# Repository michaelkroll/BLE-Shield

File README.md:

## BLE-Shield

The MIT License (MIT)
Copyright (c) 2012-2015 Dr. Michael Kroll
 
Permission is hereby granted, free of charge, to any person obtaining a copy of this software and associated 
documentation files (the "Software"), to deal in the Software without restriction, including without limitation 
the rights to use, copy, modify, merge, publish, distribute, sublicense, and/or sell copies of the Software, 
and to permit persons to whom the Software is furnished to do so, subject to the following conditions:
 
The above copyright notice and this permission notice shall be included in all copies or substantial portions of the Software.
 
THE SOFTWARE IS PROVIDED "AS IS", WITHOUT WARRANTY OF ANY KIND, EXPRESS OR IMPLIED, INCLUDING BUT NOT 
LIMITED TO THE WARRANTIES OF MERCHANTABILITY, FITNESS FOR A PARTICULAR PURPOSE AND NONINFRINGEMENT. IN 
NO EVENT SHALL THE AUTHORS OR COPYRIGHT HOLDERS BE LIABLE FOR ANY CLAIM, DAMAGES OR OTHER LIABILITY, 
WHETHER IN AN ACTION OF CONTRACT, TORT OR OTHERWISE, ARISING FROM, OUT OF OR IN CONNECTION WITH THE 
SOFTWARE OR THE USE OR OTHER DEALINGS IN THE SOFTWARE.

### Content

This repository contains the eagle design files as well as the firmware source code and precompiled hex files.
Moreover I added the Arduino Sketches from my blog to this repository.

### Latest Version

The Latest version of the BLE-Shield is v3.0.0 as illustrated in the image below.

#### Services and Characteristics of the BLE-Shield v3.0.0

The new BLE-Shield supports some new services and haracteristics. The RX and TX characteristics are not combined into one indicating Data characteristic
Moreover the Bluegiga OTA Service is supported enabling you to update the BLE-Shield over the air using e.g. the iOS App BLExplr.

##### BLE-Shield Service v3.0.0 (B4BDB998-8F4A-45F6-A407-6B48D79CFC2F)

###### Bluetooth Device Address Characteristic (B4BDB998-8F4B-45F6-A407-6B48D79CFC2F)

This characteristic is read only and used to retrieve the Bluetooth Device Address of the BLE113-M256k module.

###### Baudrate Characteristic (B4BDB998-8F4C-45F6-A407-6B48D79CFC2F)

This characteristic is read and write and used to set the BLE-Shields baudrate. The default baudrate is 9600 baud
It is a one byte characteristic. The following baudrates are suported and can be set using the following byte set to the
characteristic:

Baudrate  | Configuration Byte
--------- | ------------------
9600      | 0x00
14400     | 0x01
19200     | 0x02
28800     | 0x03
38400     | 0x04
57600     | 0x05
115200    | 0x06

###### Enable Connect LED characteristic (B4BDB998-8F4D-45F6-A407-6B48D79CFC2F)

This characteristic is used to control the connection LED on the BLE-Shield. The LED is per default off.
In order to change it's behavior write e.g. 0xff the the characteristic to make it lit on the next connection.

LED State | Configuration Byte
--------- | ------------------
OFF       | 0x00
ON        | 0xff

###### Data characteristic (B4BDB998-8F4E-45F6-A407-6B48D79CFC2F)

The new BLE-Shield v3.0.0 uses a Data characteristic to send and receive data. In order to support this
the characteristic is a write and indicate characteristic. On BLExplr it is no longer necessary to switch between
RX and TX characteristics. You can stay on the same screen to see data which is recevied while you are transmitting data.

##### Bluegiga OTA Service (1d14d6ee-fd63-4fa1-bfa4-8f47b42119f0)

This is the implementation of Bluegiga's OTA Service to update the firmware over the air.

###### Data characteristic (f7bf3564-fb6d-4e53-88a4-5e37e0326063)

Bluegiga OTA Control Characteristic

###### Data characteristic (984227f3-34fc-4045-a5d0-2c581f81a153)

Bluegiga OTA Data Characteristic

### Links
* http://www.mkroll.mobi
* http://forum.mkroll.mobi

### Notes:
* The Eagle design files are created using Eagle v5.11.0 - v7.1 depending on the version of the BLE-Shield. BLE-Shield v3.0.0 was designed with Eagle v7.1.0
* The Firmware v1.0.0 and v1.0.1 for the BLE112 module on the BLE-Shield was created and compiled for the Bluegiga BLE112 SDK v1.0.3 Build 43
* The Firmware v3.0.0 was developed using Bluegiga's BLE SDK v1.3.2 Build 122.
* The Arduino Sketches have been tested with Arduino 1.0.1
* the Arduino Sketched vor BLE-Shield v3.0.0 has been tested with Arduino v1.0.6 on OSX
* The .NETMF Sample has been tested with Microsoft Visual C# Express 2010, .NET Micro Framework SDK v4.2 and the Netduino SDK v4.2.2.0 (32-bit) running on a NetDuino2

## .NETMF support 
The latest addition to this repository is .NETMF support. With a little help of Thomas Amberg @tamberg I added a sample project for 
the NetDuino2 board available at http://www.netduino.com which shows how use the BLE-Shield with this platform.  

## BLE-Shield iPhone App for the BLE-Shield v1.0.0

The iPhone App was part of the BLE-Shield Kickstarter campaign https://www.kickstarter.com/projects/rowdyrobot/arduino-ble-shield-connecting-the-ios-and-the-ardu and only
supports the BLE-Shield v1.0.0 The BLE-Shield app provides access to the BLE-Shield Service and their characteristics. It's user interface is implemented like 
a chat application. The chart partners are the BLE-Shield and the iPhone, illustrated by small icons.

Once the BLE-Shield is connected, the application will automatically enable notifications on the RX characteristic. So whenever 
the BLE-Shield's 16 byte buffer is filled completely, the buffer will be notified to the iPhone. 

The app was developed using Xcode 4.5.2, iOS6 SDK and tested on an iPhone4S and iPhone5 running iOS6.0.1

*Screenshots*

. 
. 
. 
. 
. 
. 

### Used third party components

* BLEUtils taken from the TI SensorTag App, created by Ole Andreas Torvmark 
* MBProgressHUD created by Matej Bukovinski https://github.com/matej/MBProgressHUD
* PTSMessagingCell created by Ralph Grasser https://github.com/ppanopticon/PTSMessagingCell/

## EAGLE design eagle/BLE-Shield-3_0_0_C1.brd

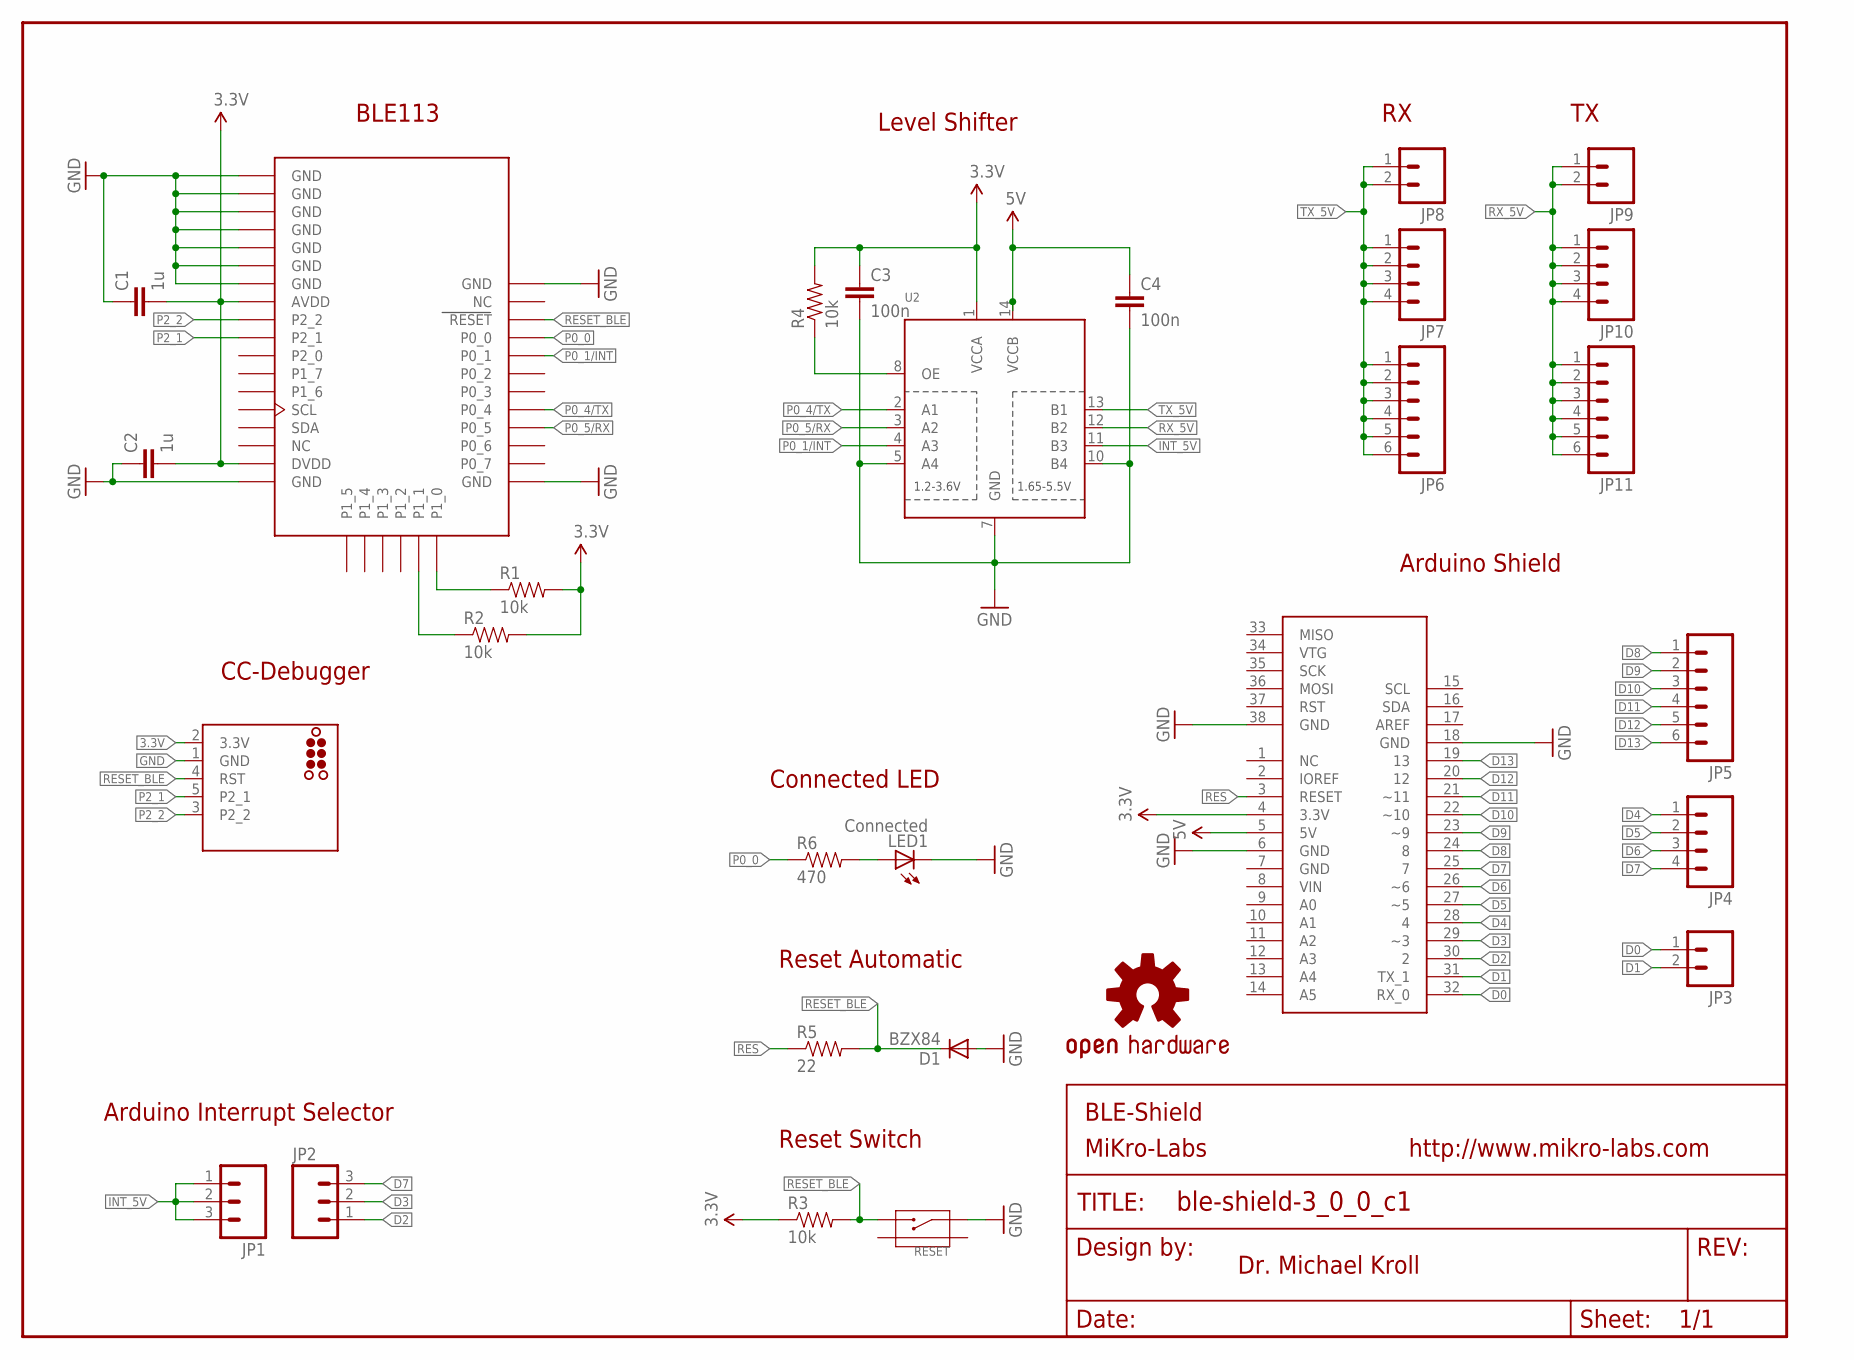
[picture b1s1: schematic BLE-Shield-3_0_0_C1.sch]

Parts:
C1, C2: 1u; 0603-CAP
C3, C4: 100n; 0603-CAP
CC-DEBUGGER: TC2030-CC-DEBUGGER; TC2030-MCP-NL
D1: BZX84; SOT23-3
FRAME1: FRAME-LETTER; CREATIVE_COMMONS
JP1, JP2: M03PTH; 1X03
JP3, JP8, JP9: M02PTH; 1X02
JP4, JP7, JP10: M04PTH; 1X04
JP5, JP6, JP11: M06SIP; 1X06
LED1: Connected; LED-0603
LOGO1: OSHW-LOGOS; OSHW-LOGO-S
R1, R2, R3, R4: 10k; 0603-RES
R5: 22; 0603-RES
R6: 470; 0603-RES
RESET: BUTTON-2P-REINFORCE-3100060P1; 4P-SMD-7.0X3.5X3.5H-90D
U1: BLE113-A-VISUAL; BLE113-A
U2: TXB0104PWR; TSSOP14
U$1: ARDUINO_UNO_SHIELD_ICSP_PADS_ONLY; ICSP_PADS_ONLY

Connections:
3.3V: C1.2, C2.2, C3.1, CC-DEBUGGER.2 (3.3V), R1.2, R2.2, R3.1, R4.2, U1.AVDD, U1.DVDD, U2.1 (VCCA), U$1.4 (3.3V)
5V: C4.1, U2.14 (VCCB), U$1.5 (5V)
D0: JP3.1, U$1.32 (RX_0)
D1: JP3.2, U$1.31 (TX_1)
D2: JP2.1, U$1.30 (2)
D3: JP2.2, U$1.29 (~3)
D4: JP4.1, U$1.28 (4)
D5: JP4.2, U$1.27 (~5)
D6: JP4.3, U$1.26 (~6)
D7: JP2.3, JP4.4, U$1.25 (7)
D8: JP5.1, U$1.24 (8)
D9: JP5.2, U$1.23 (~9)
D10: JP5.3, U$1.22 (~10)
D11: JP5.4, U$1.21 (~11)
D12: JP5.5, U$1.20 (12)
D13: JP5.6, U$1.19 (13)
GND: C1.1, C2.1, C3.2, C4.2, CC-DEBUGGER.1 (GND), D1.1 (A), LED1.C, RESET.1, U1.GND, U1.GND@2 (GND), U1.GND@3 (GND), U1.GND@4 (GND), U1.GND@5 (GND), U1.GND@6 (GND), U1.GND@7 (GND), U1.GND@8 (GND), U1.GND@9 (GND), U1.GND@10 (GND), U2.5 (A4), U2.7 (GND), U2.10 (B4), U$1.6 (GND), U$1.18 (GND), U$1.38 (GND)
INT_5V: JP1.1, JP1.2, JP1.3, U2.11 (B3)
unnamed: LED1.A, R6.2
unnamed: R4.1, U2.8 (OE)
unnamed: R1.1, U1.P1_0
unnamed: R2.1, U1.P1_1
P0_0: R6.1, U1.P0_0
P0_1/INT: U1.P0_1, U2.4 (A3)
P0_4/TX: U1.P0_4, U2.2 (A1)
P0_5/RX: U1.P0_5, U2.3 (A2)
P2_1: CC-DEBUGGER.5 (P2_1), U1.P2_1
P2_2: CC-DEBUGGER.3 (P2_2), U1.P2_2
RES: R5.1, U$1.3 (RESET)
RESET_BLE: CC-DEBUGGER.4 (RST), D1.3 (C), R3.2, R5.2, RESET.2, U1.RESET
RX_5V: JP9.1, JP9.2, JP10.1, JP10.2, JP10.3, JP10.4, JP11.1, JP11.2, JP11.3, JP11.4, JP11.5, JP11.6, U2.12 (B2)
TX_5V: JP6.1, JP6.2, JP6.3, JP6.4, JP6.5, JP6.6, JP7.1, JP7.2, JP7.3, JP7.4, JP8.1, JP8.2, U2.13 (B1)

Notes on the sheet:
BLE113
CC-Debugger
Arduino Shield
Level Shifter
Reset Switch
Reset Automatic
Connected LED
Arduino Interrupt Selector
BLE-Shield
MiKro-Labs
http://www.mikro-labs.com
Dr. Michael Kroll

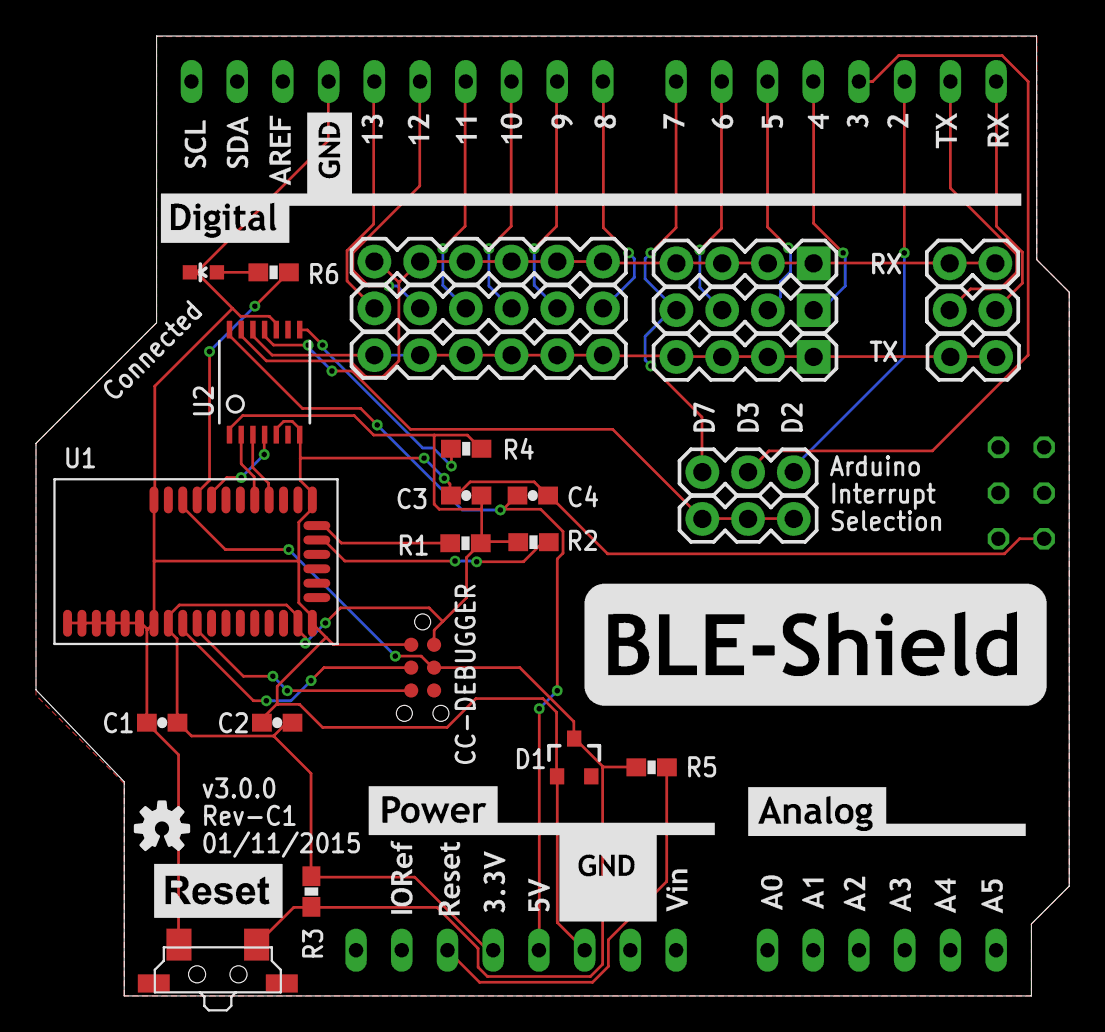
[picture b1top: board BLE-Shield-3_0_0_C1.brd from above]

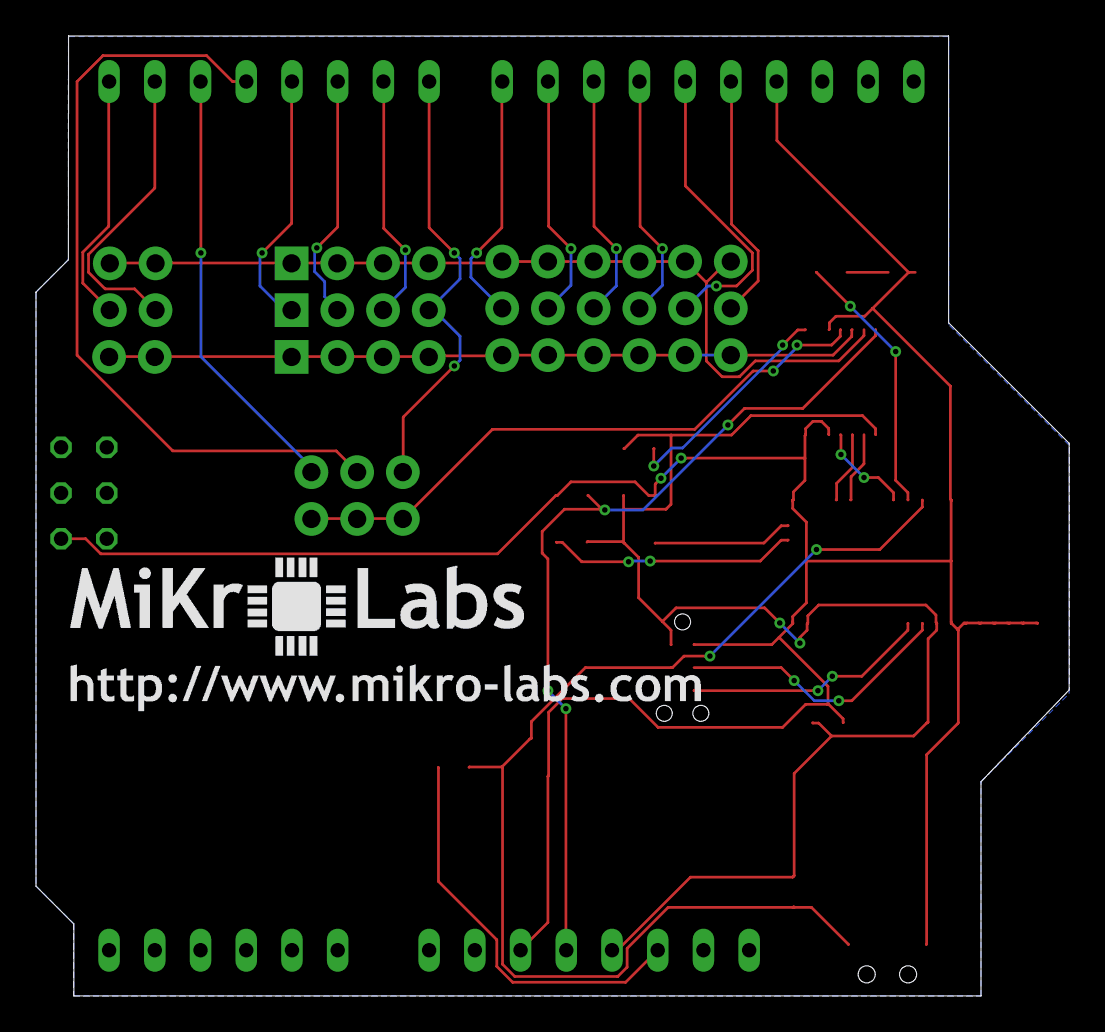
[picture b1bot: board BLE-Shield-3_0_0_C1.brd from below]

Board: 4 copper layers, 57.4 x 53.3 mm, 36 parts (2 on the bottom side), 32 nets.

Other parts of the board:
U$2: DIGITAL
U$3: POWER-ANALOG
U$4: MIKROLABS-URL
U$5: MIKROLABS-LOGO
U$6: BLE-SHIELD
U$7: RESET

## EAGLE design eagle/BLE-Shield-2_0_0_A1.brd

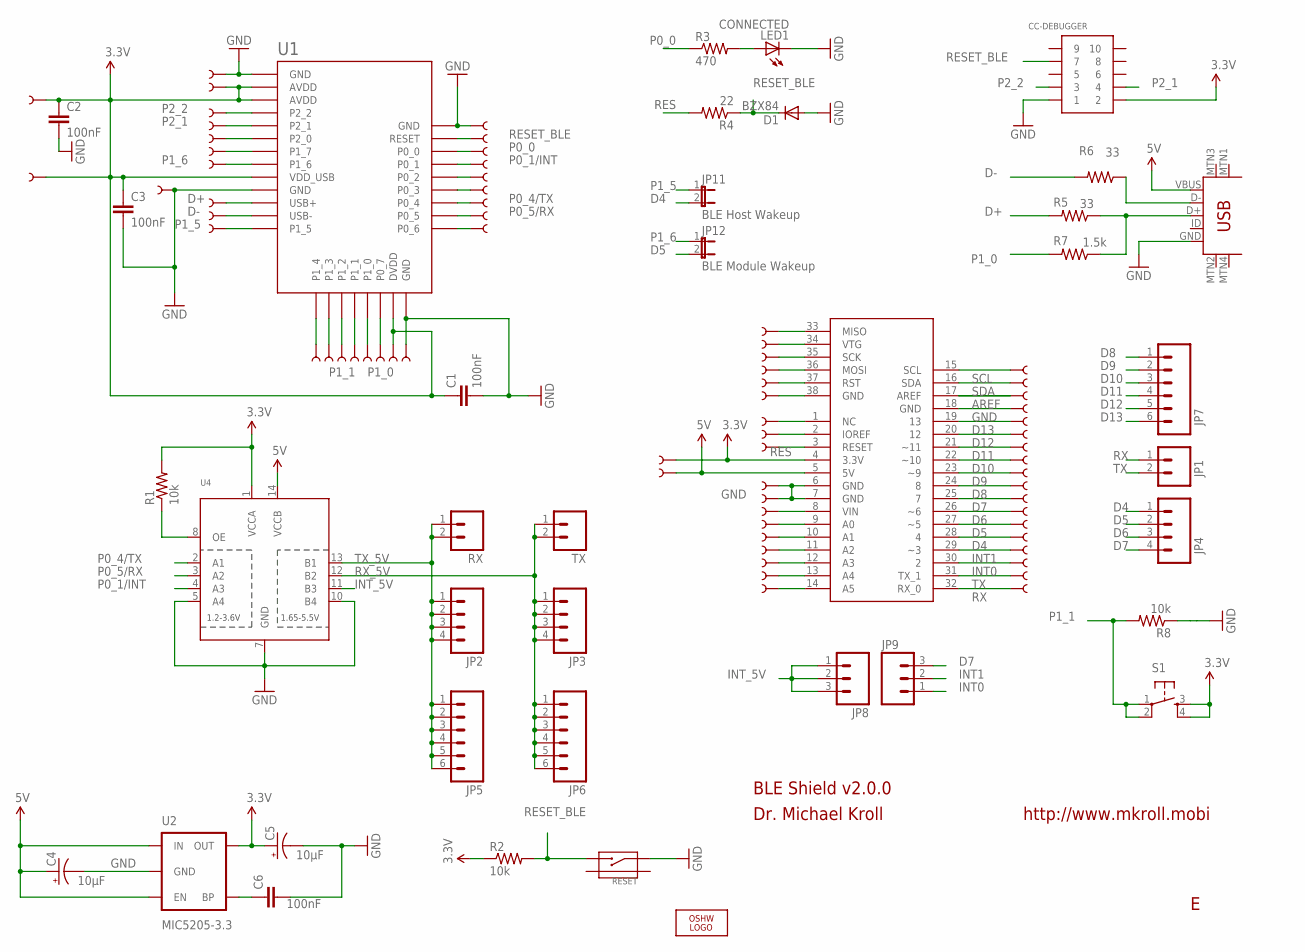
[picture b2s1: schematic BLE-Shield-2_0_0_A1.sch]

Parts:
C1, C2, C3, C6: 100nF; 0603-CAP
C4, C5: 10µF; EIA3216
CC-DEBUGGER: CONN_5-2-FTSH-V; FTSH-105-DV
D1: BZX84; SOT23-3
JP1: M02PTH; 1X02
JP2, JP3, JP4: M04PTH; 1X04
JP5, JP6, JP7: M06SIP; 1X06
JP8, JP9: M03PTH; 1X03
JP11: BLE Host Wakeup; SJ_2S-NO-NS
JP12: BLE Module Wakeup; SJ_2S-NO-NS
LED1: CONNECTED; LED-0603
LOGO1: LOGO-OSHW-FILLX0200-NT; OSHW_FILLX200_NOTEXT
R1, R2, R8: 10k; 0603-RES
R3: 470; 0603-RES
R4: 22; 0603-RES
R5, R6: 33; 0603-RES
R7: 1.5k; 0603-RES
RESET: BUTTON-2P-REINFORCE-3100060P1; 4P-SMD-7.0X3.5X3.5H-90D
RX: M02PTH; 1X02
S1: TAC_SWITCHSMD; TACTILE_SWITCH_SMD
TP1, TP2, TP3, TP4, TP5, TP6, TP7, TP8, TP9, TP10, TP11, TP12, TP13, TP14, TP15, TP16, TP17, TP18, TP19, TP20, TP21, TP22, TP23, TP24, TP25, TP26, TP27, TP28, TP29, TP30, TP31, TP32, TP33, TP34, TP35, TP36, TP37, TP38, TP39, TP40, TP41, TP42, TP43, TP44, TP45, TP46, TP47, TP48, TP49, TP50, TP51, TP52, TP53, TP54, TP55, TP56, TP57, TP58, TP59, TP60, TP61, TP62, TP63, TP64, TP65, TP66, TP67, TP68: TEST-POINT3X5; PAD.03X.05
TX: M02PTH; 1X02
U1: BLE112-A-VISUAL; BLE112-A
U2: MIC5205-3.3; SOT23-5
U4: TXB0104PWR; TSSOP14
U$5: ARDUINO_UNO_SHIELD_ICSP_PADS_ONLY; ICSP_PADS_ONLY
U$6: USB-MINIB-5PIN; USB-MINIB

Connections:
3.3V: C1.1, C2.1, C3.1, C5.A (+), CC-DEBUGGER.2, R1.2, R2.1, S1.3, S1.4, TP29.P$1, TP45.P$1, TP57.P$1, TP58.P$1, TP64.P$1, U1.AVDD1 (AVDD), U1.AVDD2 (AVDD), U1.DVDD, U1.VDD_USB, U2.5 (OUT), U4.1 (VCCA), U$5.4 (3.3V)
5V: C4.A (+), TP46.P$1, U2.1 (IN), U2.3 (EN), U4.14 (VCCB), U$5.5 (5V), U$6.VBUS
AREF: TP3.P$1, U$5.17 (AREF)
D4: JP4.1, JP11.2, TP14.P$1, U$5.28 (4)
D5: JP4.2, JP12.2, TP13.P$1, U$5.27 (~5)
D6: JP4.3, TP12.P$1, U$5.26 (~6)
D7: JP4.4, JP9.3, TP11.P$1, U$5.25 (7)
D8: JP7.1, TP10.P$1, U$5.24 (8)
D9: JP7.2, TP9.P$1, U$5.23 (~9)
D10: JP7.3, TP8.P$1, U$5.22 (~10)
D11: JP7.4, TP7.P$1, U$5.21 (~11)
D12: JP7.5, TP6.P$1, U$5.20 (12)
D13: JP7.6, TP5.P$1, U$5.19 (13)
D+: R5.2, TP66.P$1, U1.USB+
D-: R6.2, TP67.P$1, U1.USB-
GND: C1.2, C2.2, C3.2, C4.C (-), C5.C (-), C6.2, CC-DEBUGGER.1, D1.1 (A), LED1.C, R8.1, RESET.1, TP4.P$1, TP19.P$1, TP28.P$1, TP47.P$1, TP48.P$1, TP54.P$1, TP65.P$1, U1.GND1 (GND), U1.GND2 (GND), U1.GND3 (GND), U1.GND4 (GND), U2.2 (GND), U4.5 (A4), U4.7 (GND), U4.10 (B4), U$5.6 (GND), U$5.7 (GND), U$5.18 (GND), U$6.GND
INT0: JP9.1, TP16.P$1, U$5.30 (2)
INT1: JP9.2, TP15.P$1, U$5.29 (~3)
INT_5V: JP8.1, JP8.2, JP8.3, U4.11 (B3)
unnamed: TP53.P$1, U$5.12 (A3)
unnamed: C6.1, U2.4 (BP)
unnamed: TP56.P$1, U$5.14 (A5)
unnamed: LED1.A, R3.2
unnamed: TP55.P$1, U$5.13 (A4)
unnamed: TP52.P$1, U$5.11 (A2)
unnamed: TP51.P$1, U$5.10 (A1)
unnamed: TP50.P$1, U$5.9 (A0)
unnamed: TP49.P$1, U$5.8 (VIN)
unnamed: R5.1, R7.1, U$6.D+
unnamed: TP43.P$1, U$5.2 (IOREF)
unnamed: TP27.P$1, U1.P0_6
unnamed: TP35.P$1, U1.P1_4
unnamed: TP24.P$1, U1.P0_3
unnamed: TP23.P$1, U1.P0_2
unnamed: TP42.P$1, U$5.1 (NC)
unnamed: TP34.P$1, U1.P1_3
unnamed: TP33.P$1, U1.P1_2
unnamed: TP30.P$1, U1.P0_7
unnamed: TP41.P$1, U$5.38 (GND)
unnamed: TP40.P$1, U$5.37 (RST)
unnamed: TP39.P$1, U$5.36 (MOSI)
unnamed: TP38.P$1, U$5.35 (SCK)
unnamed: TP37.P$1, U$5.34 (VTG)
unnamed: TP36.P$1, U$5.33 (MISO)
unnamed: R6.1, U$6.D-
unnamed: TP61.P$1, U1.P2_0
unnamed: TP62.P$1, U1.P1_7
unnamed: R1.1, U4.8 (OE)
P0_0: R3.1, TP21.P$1, U1.P0_0
P0_1/INT: TP22.P$1, U1.P0_1, U4.4 (A3)
P0_4/TX: TP25.P$1, U1.P0_4, U4.2 (A1)
P0_5/RX: TP26.P$1, U1.P0_5, U4.3 (A2)
P1_0: R7.2, TP31.P$1, U1.P1_0
P1_1: R8.2, S1.1, S1.2, TP32.P$1, U1.P1_1
P1_5: JP11.1, TP68.P$1, U1.P1_5
P1_6: JP12.1, TP63.P$1, U1.P1_6
P2_1: CC-DEBUGGER.4, TP60.P$1, U1.P2_1
P2_2: CC-DEBUGGER.3, TP59.P$1, U1.P2_2
RES: R4.2, TP44.P$1, U$5.3 (RESET)
RESET_BLE: CC-DEBUGGER.7, D1.3 (C), R2.2, R4.1, RESET.2, TP20.P$1, U1.RESET
RX: JP1.1, TP18.P$1, U$5.32 (RX_0)
RX_5V: JP3.1, JP3.2, JP3.3, JP3.4, JP6.1, JP6.2, JP6.3, JP6.4, JP6.5, JP6.6, TX.1, TX.2, U4.12 (B2)
SCL: TP1.P$1, U$5.15 (SCL)
SDA: TP2.P$1, U$5.16 (SDA)
TX: JP1.2, TP17.P$1, U$5.31 (TX_1)
TX_5V: JP2.1, JP2.2, JP2.3, JP2.4, JP5.1, JP5.2, JP5.3, JP5.4, JP5.5, JP5.6, RX.1, RX.2, U4.13 (B1)

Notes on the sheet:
BLE Shield v2.0.0
Dr. Michael Kroll
http://www.mkroll.mobi

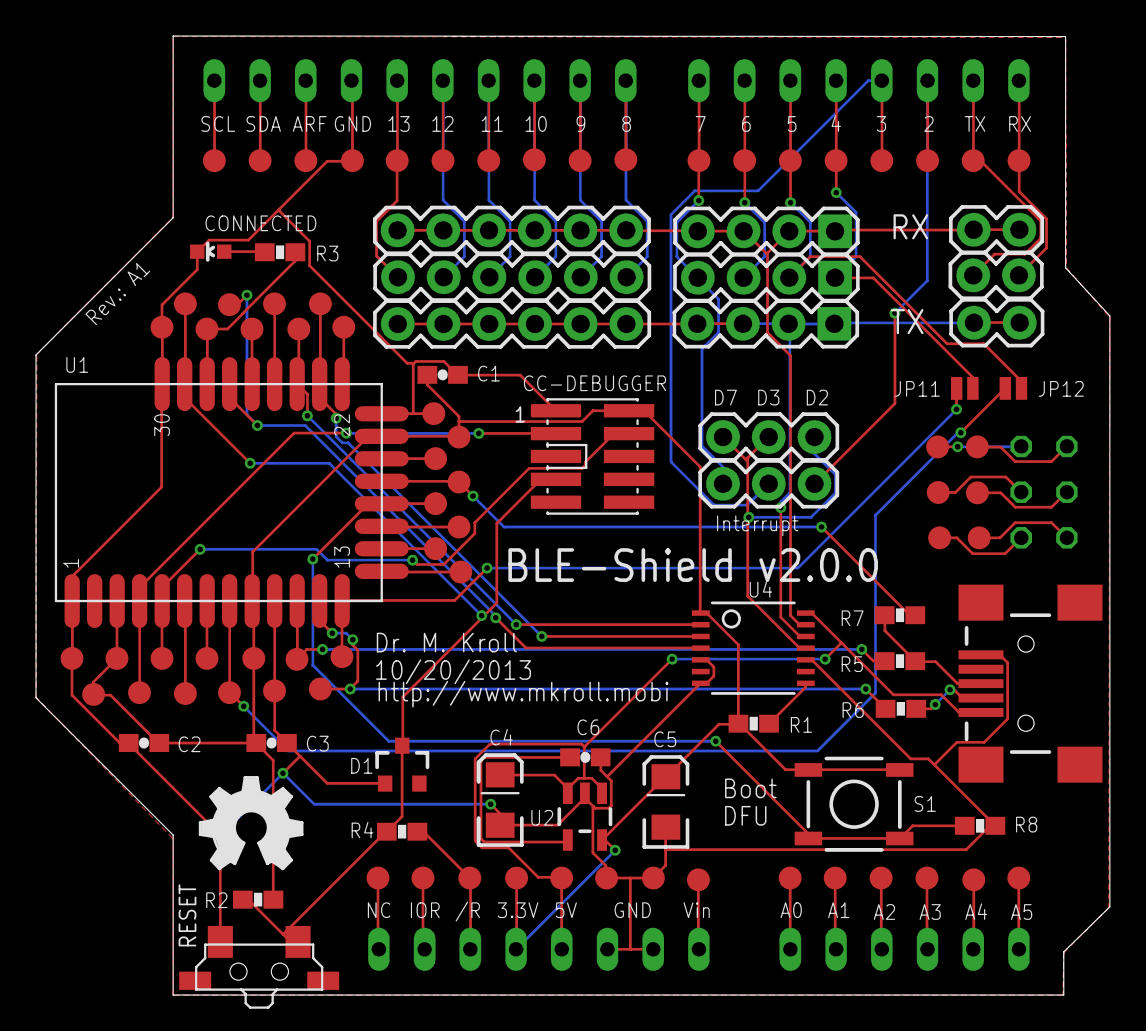
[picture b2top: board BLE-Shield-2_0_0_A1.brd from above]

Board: 4 copper layers, 59.7 x 53.3 mm, 106 parts (0 on the bottom side), 66 nets.

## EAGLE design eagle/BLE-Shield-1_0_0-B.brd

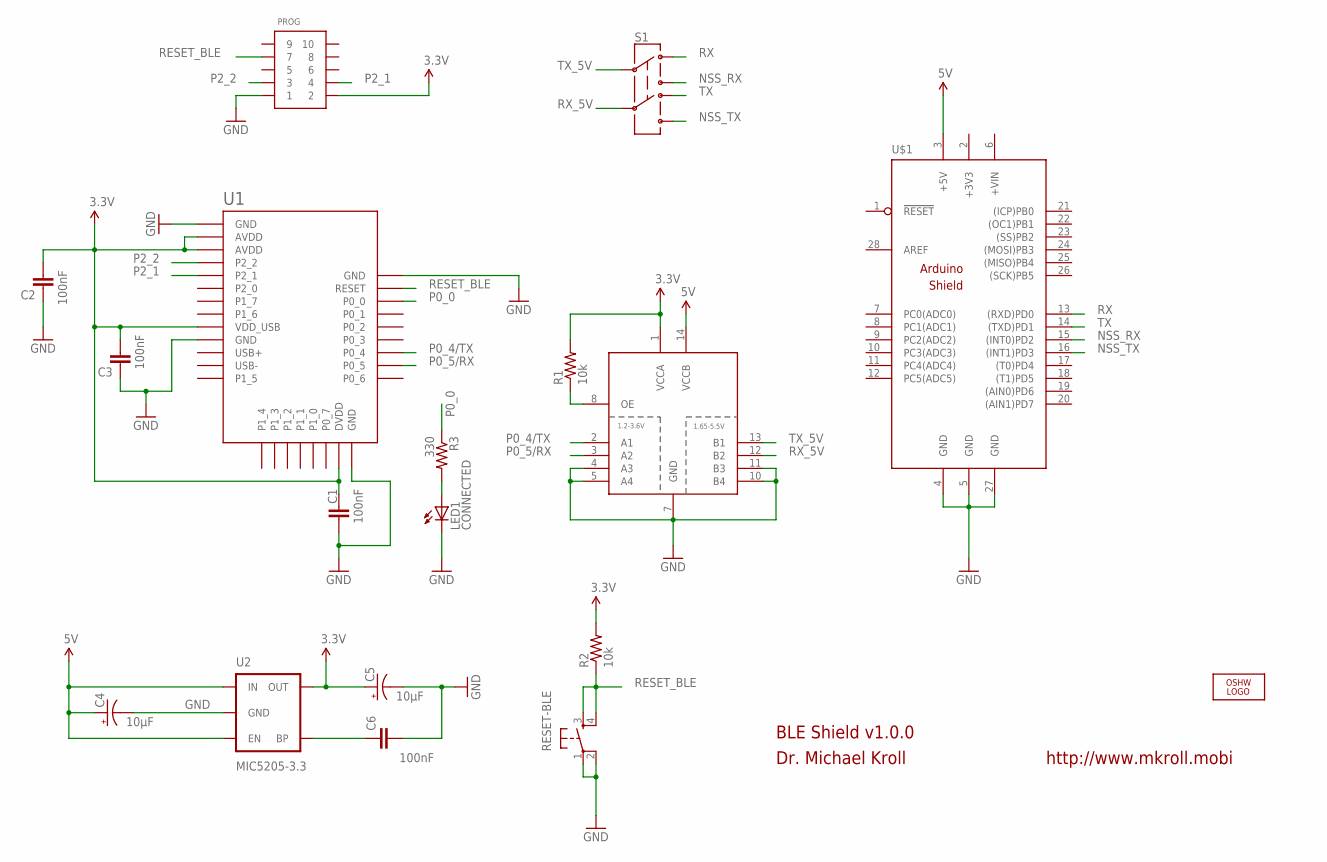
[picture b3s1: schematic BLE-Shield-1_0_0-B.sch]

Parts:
C1, C2, C3, C6: 100nF; 1206
C4, C5: 10µF; EIA3216
LED1: CONNECTED; LED-1206-BLUE
LOGO1: LOGO-OSHW-FILLX0200-NT; OSHW_FILLX200_NOTEXT
PROG: CONN_5-2-FTSH-V; FTSH-105-DV
R1, R2: 10k; 0805
R3: 330; 0805
RESET-BLE: TAC_SWITCHSMD; TACTILE_SWITCH_SMD
S1: SWITCH-DPDTSMD; AYZ0202
U1: BLE112-A-VISUAL; BLE112-A
U2: MIC5205-3.3; SOT23-5
U3: TXB0104DR; SO14
U$1: ARDUINO_SHIELD

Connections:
3.3V: C1.2, C2.2, C3.2, C5.A (+), PROG.2, R1.2, R2.2, U1.AVDD1 (AVDD), U1.AVDD2 (AVDD), U1.DVDD, U1.VDD_USB, U2.5 (OUT), U3.1 (VCCA)
5V: C4.A (+), U2.1 (IN), U2.3 (EN), U3.14 (VCCB), U$1.3 (+5V)
+3V3: U$1.2 (+3V3)
GND: C1.1, C2.1, C3.1, C4.C (-), C5.C (-), C6.2, LED1.C, PROG.1, RESET-BLE.1, RESET-BLE.2, U1.GND1 (GND), U1.GND2 (GND), U1.GND3 (GND), U1.GND4 (GND), U2.2 (GND), U3.4 (A3), U3.5 (A4), U3.7 (GND), U3.10 (B4), U3.11 (B3), U$1.4 (GND), U$1.5 (GND), U$1.27 (GND)
unnamed: C6.1, U2.4 (BP)
unnamed: LED1.A, R3.2
unnamed: R1.1, U3.8 (OE)
NSS_RX: S1.3, U$1.15 ((INT0)PD2)
NSS_TX: S1.6, U$1.16 ((INT1)PD3)
P0_0: R3.1, U1.P0_0
P0_4/TX: U1.P0_4, U3.2 (A1)
P0_5/RX: U1.P0_5, U3.3 (A2)
P2_1: PROG.4, U1.P2_1
P2_2: PROG.3, U1.P2_2
RESET_BLE: PROG.7, R2.1, RESET-BLE.3, RESET-BLE.4, U1.RESET
RX: S1.1, U$1.13 ((RXD)PD0)
RX_5V: S1.5, U3.12 (B2)
TX: S1.4, U$1.14 ((TXD)PD1)
TX_5V: S1.2, U3.13 (B1)

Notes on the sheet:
BLE Shield v1.0.0
Dr. Michael Kroll
http://www.mkroll.mobi

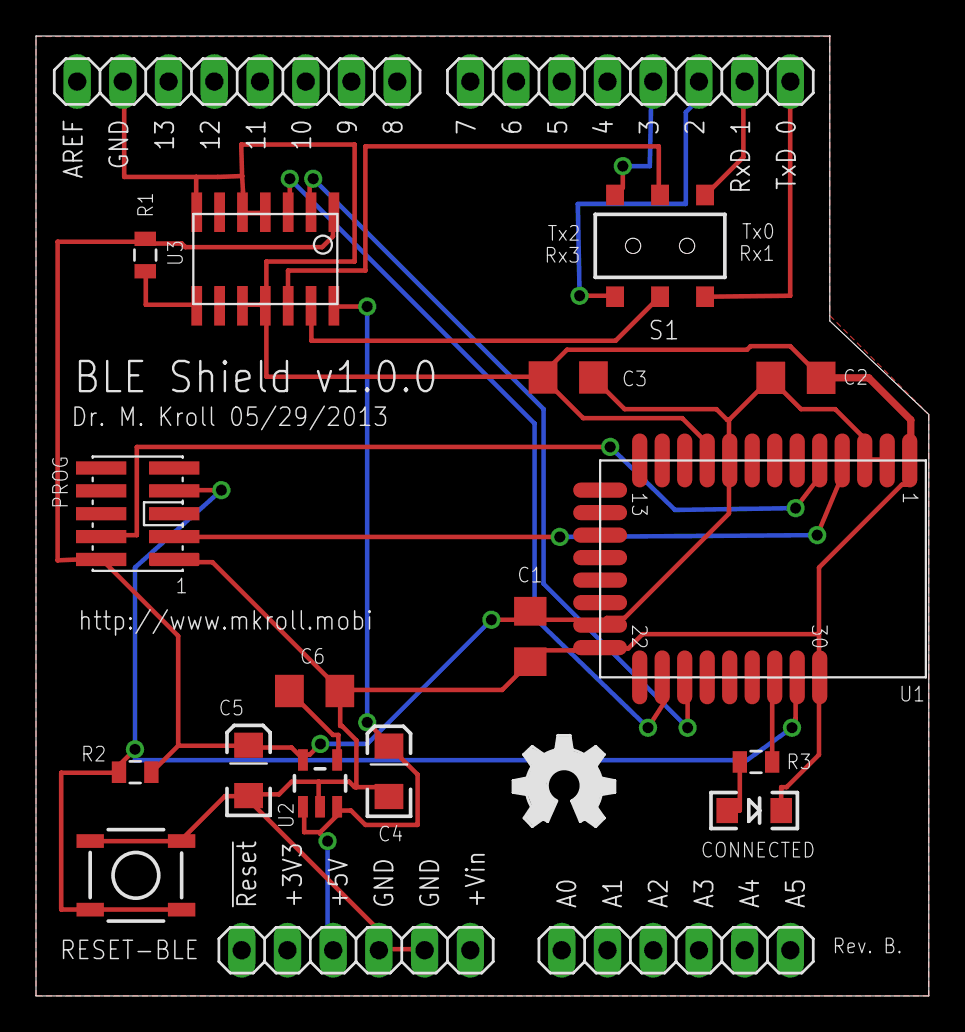
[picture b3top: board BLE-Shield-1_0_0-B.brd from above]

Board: 2 copper layers, 49.6 x 53.3 mm, 18 parts (0 on the bottom side), 18 nets.

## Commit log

2012-10-20 Initial commit containing v1.0.0 of the firmware, that will be flashed to the Kickstarter BLE-Shields.
2012-10-20 init
2012-10-21 Eagle design files added.
2012-10-21 PDF schematic added.
2012-10-21 Added some version notes for the eagle design files and the firmware.
2012-10-21 reformatted.
2012-10-25 Arduino Test Sketches added.
2012-10-25 Typo fixed
2013-01-06 Version 1.0.0 build 20 of the iPhone App finished.
2013-01-06 Missing files added.
2013-01-06 Finished v1.0.0
2013-01-06 Typo fixed.
2013-01-13 project files changed
2013-01-15 Update arduino/BLEShieldHWS/BLEShieldHWS.ino
    At least on a Arduino Mega I couldn't get this to work without setting the pin mode
2013-02-02 Leonardo Sketch added.
2013-02-11 Code for NetDuino2 added. Thanks @tamberg for helping :-)
2013-02-11 Removed some unused files.
2013-03-01 Version 1.0.1 of the firmware released with better internal buffer management.
2013-04-28 last changes
2013-05-28 New firmware for the BLE-Shield v1.0.0 Revision B with slightly modified via positions and silkscreen adjustments.
2013-08-18 v1.1.0 of the BLE-Shields firmware added.
2013-08-22 fixed the wrong version number of the service.
2013-09-23 License changed to MIT
2013-09-27 added speed testing, extra logging
2013-09-27 updated arduino and iphone apps for firmware v1.1.0
2013-09-27 Added automatic baud rate change. Doesn't work for some reason. Is the UUID correct?
2013-09-27 updated other arduino sketches with new baud rate
2013-09-27 improved speed test with rhythm. changed baud rate byte conversion
2013-10-01 BETA version of the firmware for the BLE-Shield v2.0.0
2013-10-01 BETA version of the firmware for the BLE-Shield v2.0.0 added.
2013-10-01 removed.
2013-10-01 BETA version 2.0.0 of the firmware for the BLE-Shield v2.0.0
2013-10-01 added
2013-10-01 removed temporarly.
2013-10-01 License texts changed.
2013-10-20 Two new sample sketches added for Arduino Leonardo and Arduino Uno.
2013-11-03 Removed the old firmware. Added Eagle Design files.
2013-11-03 Latest firmware based on Bluegiga's SDK 1.2.1 B91 added.
2013-11-30 latest commit.
2013-12-08 Sample sketch for BLE-Shield v1.0.0 with Firmware v1.1.0 added.
2014-02-01 updated to sdk v1.2.1 Build91
2014-02-03 Initial Version of the iBeacon firmware for the BLE-Shield v2.0.0
2014-02-24 Updated BLEShieldSS to include setting the pinModes
2014-04-18 initial version of the BLE-Shield v2.0.0 ANCS Firmware added. It is still under development, but notifications are already received on the Arduino. Access methods to get the title, message, appid etc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
2014-04-18 Initial work in progress version of an ANCS library for Arduino added.
2014-08-13 Latest changes.
2014-10-13 new projects for the BLE-Shield v3.0.0 added. Still WIP since the boards are not yet final and the firmware and hardware for the BLE-Shield v3.0.0 LR needs to be tested regarding range.
2015-02-07 Initial version of the v3.0.0 firmware finished. Added the eagle design files of revision C1 and the Arduino Sample Sketch.
2015-02-07 Documentation updated to contain the BLE-Shield v3.0.0
2015-02-07 Description updated to describe the BLE-Shield v3.0.0

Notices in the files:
parts and their libraries:
SparkFun-Capacitors: Licensing: CC v3.0 Share-Alike You are welcome to use this library for commercial purposes.
Tag-Connect: ©2009 ROFA.cz - modified and updated by Robert Darlington ‹rdarlington@gmail.com›
